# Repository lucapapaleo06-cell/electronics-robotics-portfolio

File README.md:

# Electronics & Robotics Portfolio

Electronic Engineering student at **Politecnico di Torino**, currently at **Tongji University** through the **POLITONG** program.

I was part of the **embedded branch of [Team ISAAC](https://github.com/Team-Isaac-Polito)** (2025–2026), where I designed the team's [LoRa remote kill switch](pcb-lora-kill-switch/). The team took part in the **RoboCup 2026 Rescue Robot League** in Korea, finishing **21st** as the **only Italian team**.

This repository collects my personal electronics and robotics projects: PCB design, embedded firmware and computer vision.

## Projects

| Project | What it is | Technologies | Status |
|---|---|---|---|
| [RoboCup Junior Rescue Line robot](robocup-junior-rescue-line/) | Line-following robot with computer vision for green intersection markers, plus a custom line-sensor PCB and 3D-printed chassis (team project) | Arduino, Raspberry Pi, Python, OpenCV, TensorFlow Lite, KiCad | Competed for three seasons, reached the national finals in the last one |
| [Arduino Mega shield](pcb-arduino-mega-shield/) | Main board of the RoboCup Junior robot: plugs onto an Arduino Mega and wires up sensors, motor driver and servos | KiCad, Gerber | Manufactured and used in competition |
| [LoRa remote kill switch](pcb-lora-kill-switch/) | Transmitter and receiver boards for a wireless emergency stop (Team ISAAC) | Altium Designer, RP2040, LoRa | Manufactured and tested |
| [Vision-controlled robotic hand](vision-robotic-hand/) | A webcam tracks my hand and a 5-servo robotic hand copies the finger positions | Python, OpenCV, MediaPipe, Arduino | Prototype |

The RoboCup Junior robot and its Mega shield were built together with Niccolò, Eleonora, Francesco and Ercolini.

## Repository layout

```
pcb-arduino-mega-shield/      KiCad project, schematic and PCB PDFs, Gerber files
pcb-lora-kill-switch/         Schematic + PCB PDFs, layout images, interactive 3D PDFs
vision-robotic-hand/          Python hand tracking + Arduino servo firmware
robocup-junior-rescue-line/   Arduino firmware, Raspberry Pi vision, line-sensor PCB, STL files
media/                        Renders and images used in the READMEs
```

## Tools

KiCad · Altium Designer · Arduino · Raspberry Pi · RP2040 · Python · OpenCV · MediaPipe · TensorFlow Lite · 3D printing

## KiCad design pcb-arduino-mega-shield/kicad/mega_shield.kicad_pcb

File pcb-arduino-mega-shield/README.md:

# Arduino Mega Shield

Main interface board for my RoboCup Junior Rescue Line robot ([robocup-junior-rescue-line](../robocup-junior-rescue-line/)). It plugs onto an **Arduino Mega**. It replaces loose jumper wires with labelled connectors for every sensor and actuator on the robot.

Part of the RoboCup Junior project built together with **Niccolò, Eleonora, Francesco and Ercolini** (their names are on the silkscreen, next to the team logo).

## Connectors on the board

- 3 × I²C headers for **VL53L0X time-of-flight** distance sensors (SDA/SCL)
- **Gyroscope** header with interrupt pin
- 2 × **TCS3200 colour sensor** headers (S0–S3, OUT, LED)
- Line-sensor input header on analog pins A1–A7
- **TB6612FNG motor driver** header (PWM A/B) and motor outputs
- 2 × **servo** headers
- 12 V power input

## Files

| Path | Content |
|---|---|
| `kicad/` | KiCad project (`.kicad_pro`, `.kicad_sch`, `.kicad_pcb`) |
| `images/mega_shield_schematic.pdf` | Schematic, exported with `kicad-cli` |
| `images/mega_shield_pcb.pdf` | PCB prints, one page per layer (front copper, back copper, silkscreen, outline) |
| `images/mega_shield_layout.svg` | Copper and silkscreen layout |
| `fabrication/mega_shield_gerber.zip` | Gerber and drill files for manufacturing |

## Tools

KiCad (the shield outline uses the Arduino Due/Mega form factor symbol)

## Status

Manufactured and used in competition.

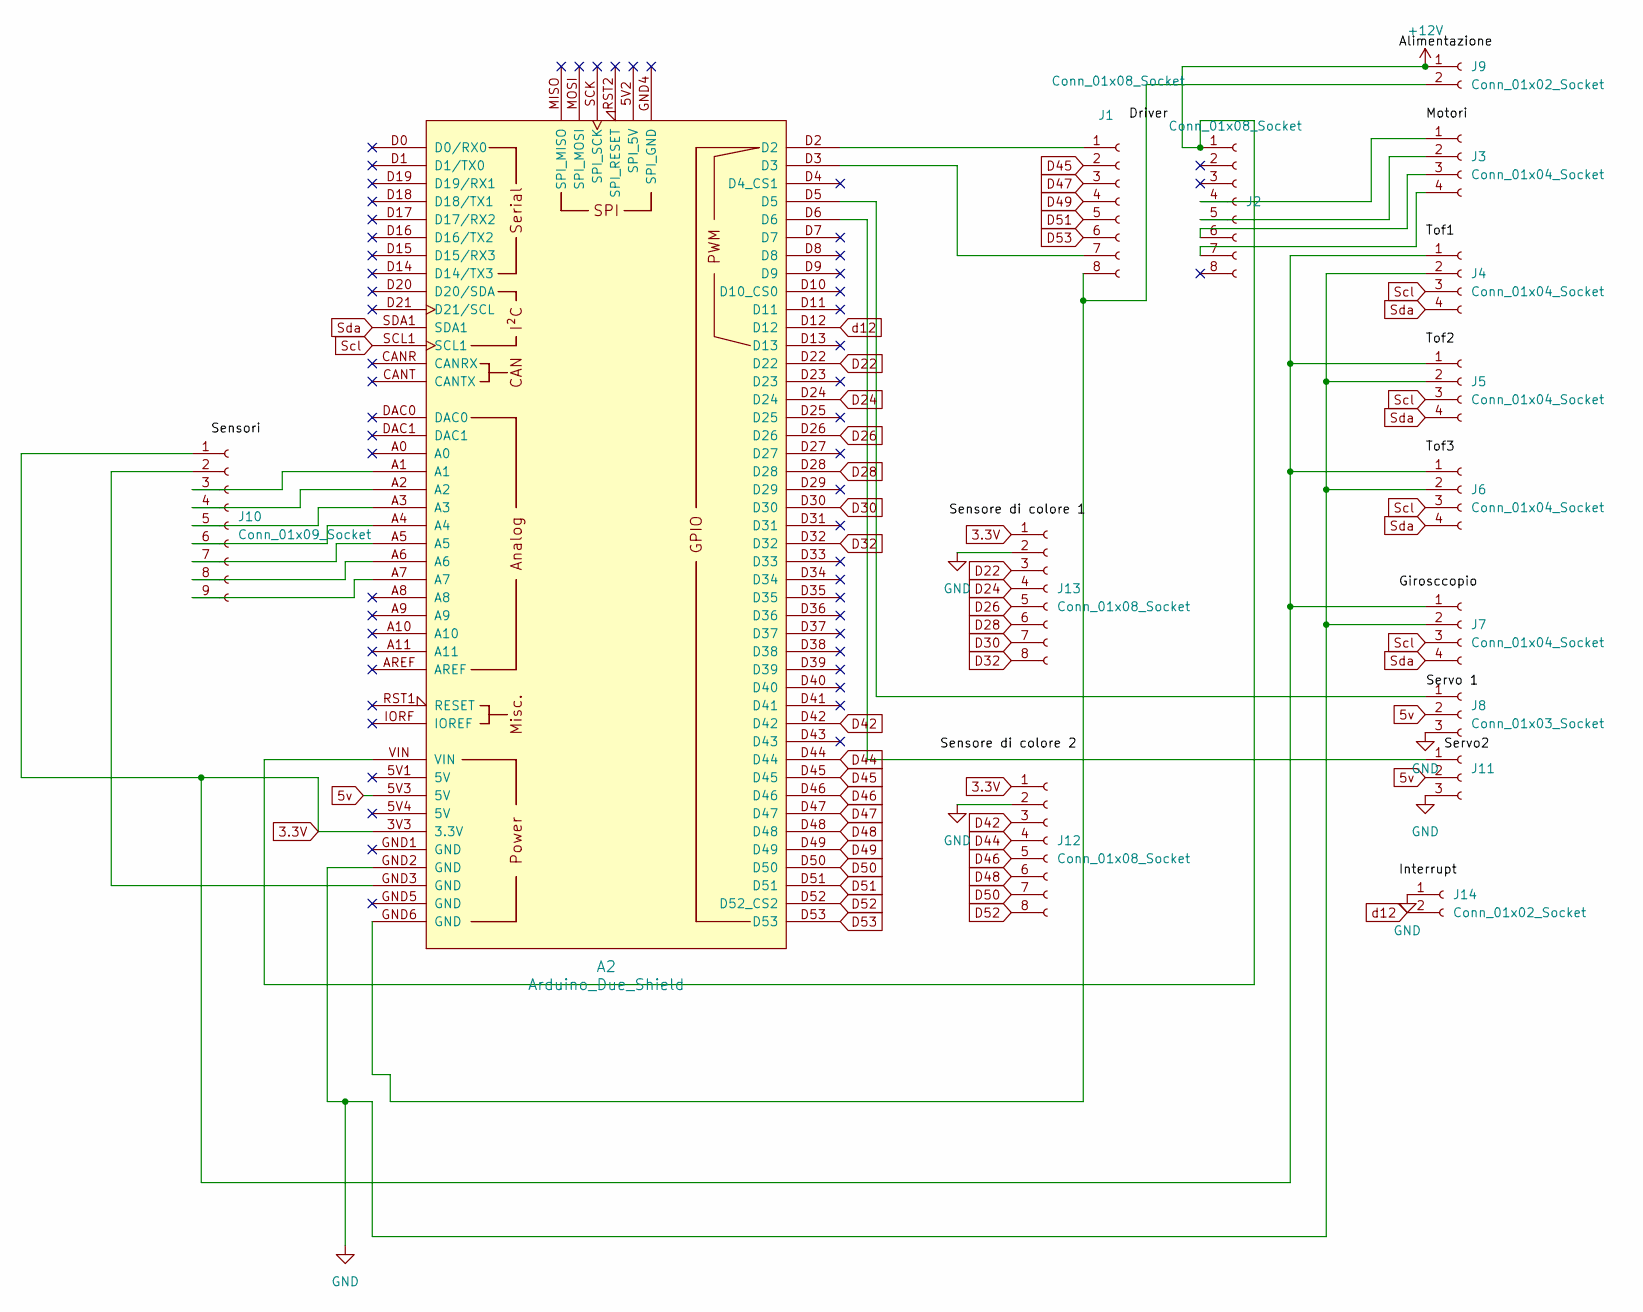
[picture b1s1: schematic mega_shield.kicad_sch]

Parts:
A2: Arduino_Due_Shield
J1, J2, J12, J13: Conn_01x08_Socket; PinSocket_1x08_P2.54mm_Vertical
J3, J4, J5, J6, J7: Conn_01x04_Socket; PinSocket_1x04_P2.54mm_Vertical
J8, J11: Conn_01x03_Socket; PinSocket_1x03_P2.54mm_Vertical
J9: Conn_01x02_Socket; AMASS_XT30UPB-F_1x02_P5.0mm_Vertical
J10: Conn_01x09_Socket; PinSocket_1x09_P2.54mm_Vertical
J14: Conn_01x02_Socket; PinSocket_1x02_P2.54mm_Vertical

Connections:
3.3V: A2.3V3 (3.3V), J4.1, J5.1, J6.1, J7.1, J10.1, J12.1, J13.1
5v: A2.5V3 (5V), J8.2, J11.2
+12V: A2.VIN, J2.1, J9.1
D22: A2.D22, J13.3
D24: A2.D24, J13.4
D26: A2.D26, J13.5
D28: A2.D28, J13.6
D30: A2.D30, J13.7
D32: A2.D32, J13.8
D42: A2.D42, J12.3
D44: A2.D44, J12.4
D45: A2.D45, J1.2
D46: A2.D46, J12.5
D47: A2.D47, J1.3
D48: A2.D48, J12.6
D49: A2.D49, J1.4
D50: A2.D50, J12.7
D51: A2.D51, J1.5
D52: A2.D52 (D52_CS2), J12.8
D53: A2.D53, J1.6
GND: A2.GND2 (GND), J4.2, J5.2, J6.2, J7.2, J8.3, J11.3, J12.2, J13.2, J14.1
unnamed: A2.D2, J1.1
unnamed: A2.D3, J1.7
unnamed: A2.GND6 (GND), J1.8, J9.2
unnamed: J2.4, J3.1
unnamed: J2.5, J3.2
unnamed: J2.6, J3.3
unnamed: J2.7, J3.4
unnamed: A2.D5, J8.1
unnamed: A2.GND3 (GND), J10.2
unnamed: A2.A1, J10.3
unnamed: A2.A2, J10.4
unnamed: A2.A3, J10.5
unnamed: A2.A4, J10.6
unnamed: A2.A5, J10.7
unnamed: A2.A6, J10.8
unnamed: A2.A7, J10.9
unnamed: A2.D6, J11.1
Scl: A2.SCL1, J4.3, J5.3, J6.3, J7.3
Sda: A2.SDA1, J4.4, J5.4, J6.4, J7.4
d12: A2.D12, J14.2

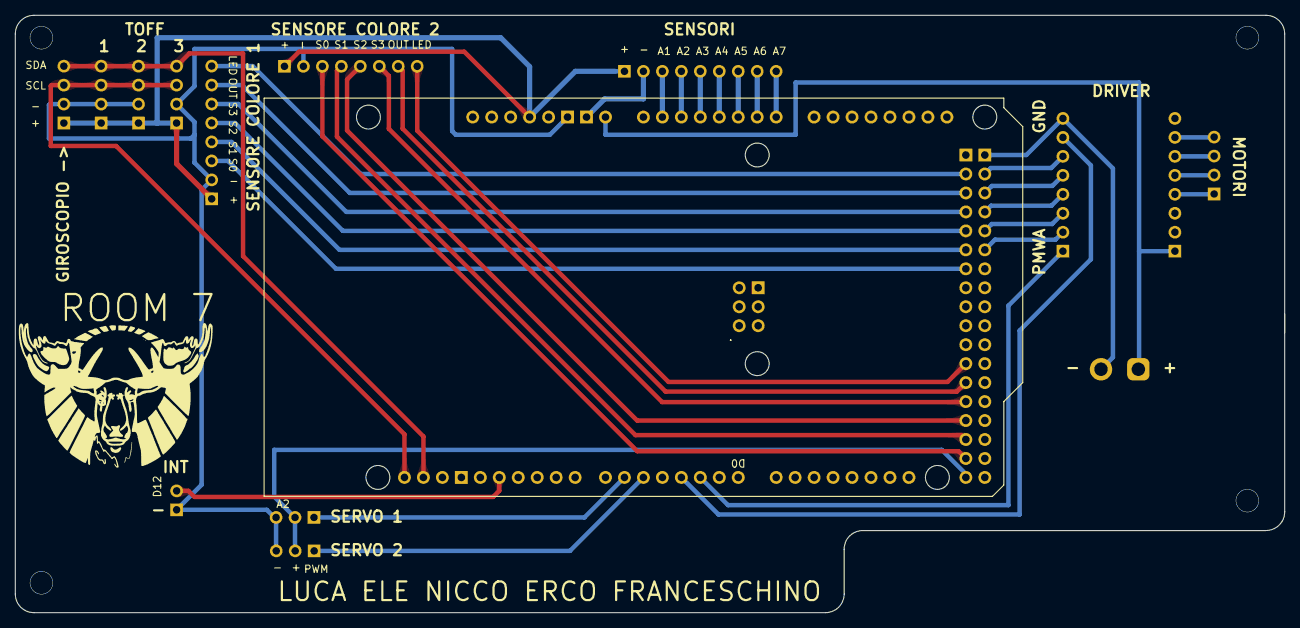
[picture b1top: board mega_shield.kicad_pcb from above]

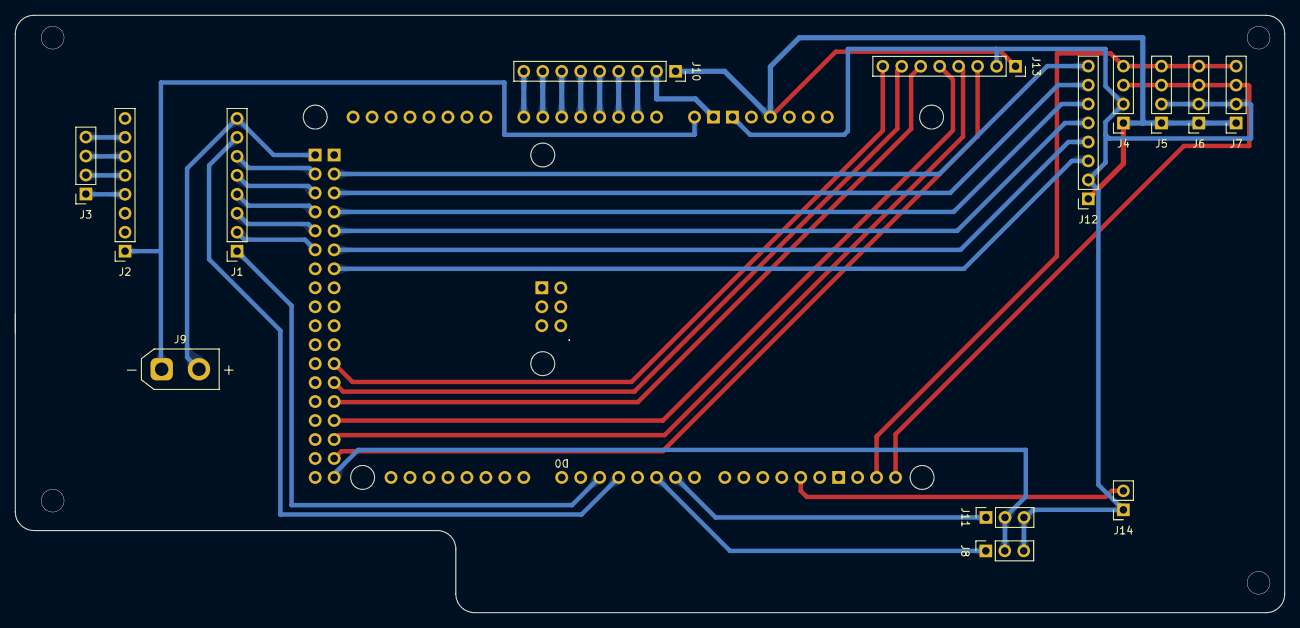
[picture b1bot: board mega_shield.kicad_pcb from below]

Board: 2 copper layers, 170.0 x 80.0 mm, 15 parts (15 on the bottom side), 41 nets.

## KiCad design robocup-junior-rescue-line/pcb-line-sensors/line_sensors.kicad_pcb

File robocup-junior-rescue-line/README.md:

# RoboCup Junior Rescue Line Robot – "Blecaut"

Autonomous robot for the **RoboCup Junior Rescue Line** challenge. Our team **competed for three seasons** and **reached the national finals** in the last one.

The robot follows a black line, handles green intersection markers and avoids obstacles. An **Arduino** runs the low-level control and a **Raspberry Pi** with a camera runs the computer vision. The two talk over serial.

## Team

Built together with **Niccolò, Eleonora, Francesco and Ercolini**. The robot, its boards and its code are a shared team effort.

## Contents

### `arduino/`: low-level control
| Sketch | Role |
|---|---|
| `seguiline_finale_sensori_di_colore_1.0` | Final line-following firmware (Arduino Mega): reflective line sensors, 2 × TCS3200 colour sensors for green markers, TB6612FNG motor driver, serial commands from the Raspberry Pi |
| `ultimo_nano_sensori_seguilinea_motori_12` | Line-following firmware for the Arduino Nano version of the robot |
| `2_seguilinea_completo_toff_seriale_1.0` | Line following with 2 × VL53L0X time-of-flight sensors for obstacle detection |
| `2_settaggio_sensori_di_colore_1.0` | Calibration tool for the colour sensors |

### `raspberry-pi/`: computer vision
| File | Role |
|---|---|
| `green_marker_detection.py` | Finds green markers and the black line using combined HSV + LAB masks. Uses contour geometry to decide the direction: **A**vanti (straight), **S**inistra (left), **D**estra (right), **I**nversione (U-turn). Sends it to the Arduino over serial |
| `color_calibration.py` | Trackbar tool to tune HSV/LAB thresholds on the field |
| `ball_detection.py` | Detects the balls in the evacuation zone with colour masks and Hough circles |
| `green_marker_classifier/` | TensorFlow Lite image classifier with the same four direction classes (A, I, D, S) |

### `pcb-line-sensors/`: custom line sensor board
8 × **CNY70** reflective sensors in an arc, with their resistors and a trimmer, on a single 8-pin output header. KiCad project, schematic and per-layer PCB PDFs (`images/`) and Gerber files (`fabrication/`). The main robot board is the [Arduino Mega shield](../pcb-arduino-mega-shield/).

### `3d/`: 3D-printed parts
Chassis body and cover (v2.2), wheel and motor gear, designed for 3D printing.

## Hardware

Arduino Mega / Arduino Nano · Raspberry Pi + camera · TB6612FNG motor driver · TCS3200 colour sensors · VL53L0X ToF sensors · CNY70 line sensors · gyroscope

## Software

Arduino (C++) · Python 3 · OpenCV · pyserial · TensorFlow Lite · KiCad

Serial ports in the Python scripts (`COM12`) are set for my development PC. Change them for the Raspberry Pi.

## Status

Competed for three seasons, reaching the national finals in the last one. The folders contain the final versions of the firmware and vision code.

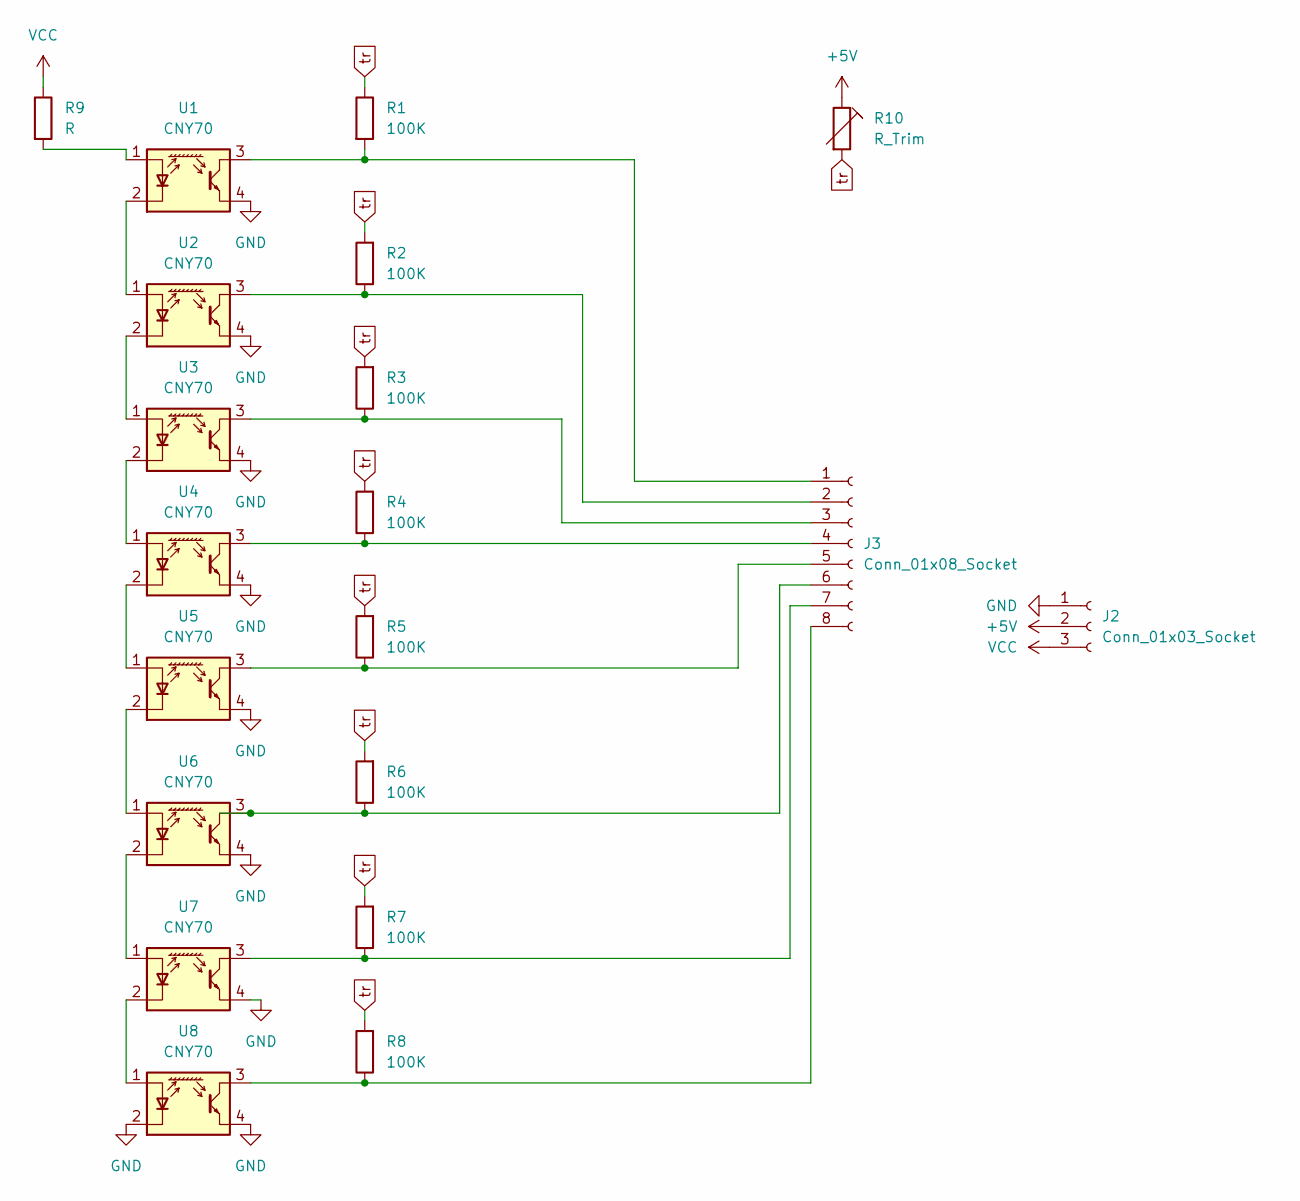
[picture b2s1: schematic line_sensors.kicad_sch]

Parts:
J2: Conn_01x03_Socket; PinSocket_1x03_P2.54mm_Vertical
J3: Conn_01x08_Socket; PinSocket_1x08_P2.54mm_Vertical
R1, R2, R3, R4, R5, R6, R7, R8: 100K; R_Axial_DIN0207_L6.3mm_D2.5mm_P7.62mm_Horizontal
R9: R; R_Axial_DIN0207_L6.3mm_D2.5mm_P7.62mm_Horizontal
R10: R_Trim; Potentiometer_Bourns_3296Y_Vertical
U1, U2, U3, U4, U5, U6, U7, U8: CNY70; Vishay_CNY70

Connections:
+5V: J2.2, R10.1
GND: J2.1, U1.4 (E), U2.4 (E), U3.4 (E), U4.4 (E), U5.4 (E), U6.4 (E), U7.4 (E), U8.2 (K), U8.4 (E)
unnamed: J3.1, R1.2, U1.3 (C)
unnamed: J3.2, R2.1, U2.3 (C)
unnamed: J3.3, R3.1, U3.3 (C)
unnamed: J3.4, R4.1, U4.3 (C)
unnamed: J3.5, R5.1, U5.3 (C)
unnamed: J3.6, R6.1, U6.3 (C)
unnamed: J3.7, R7.1, U7.3 (C)
unnamed: J3.8, R8.1, U8.3 (C)
unnamed: R9.2, U1.1 (A)
unnamed: U1.2 (K), U2.1 (A)
unnamed: U2.2 (K), U3.1 (A)
unnamed: U3.2 (K), U4.1 (A)
unnamed: U4.2 (K), U5.1 (A)
unnamed: U5.2 (K), U6.1 (A)
unnamed: U6.2 (K), U7.1 (A)
unnamed: U7.2 (K), U8.1 (A)
VCC: J2.3, R9.1
tr: R1.1, R2.2, R3.2, R4.2, R5.2, R6.2, R7.2, R8.2, R10.2

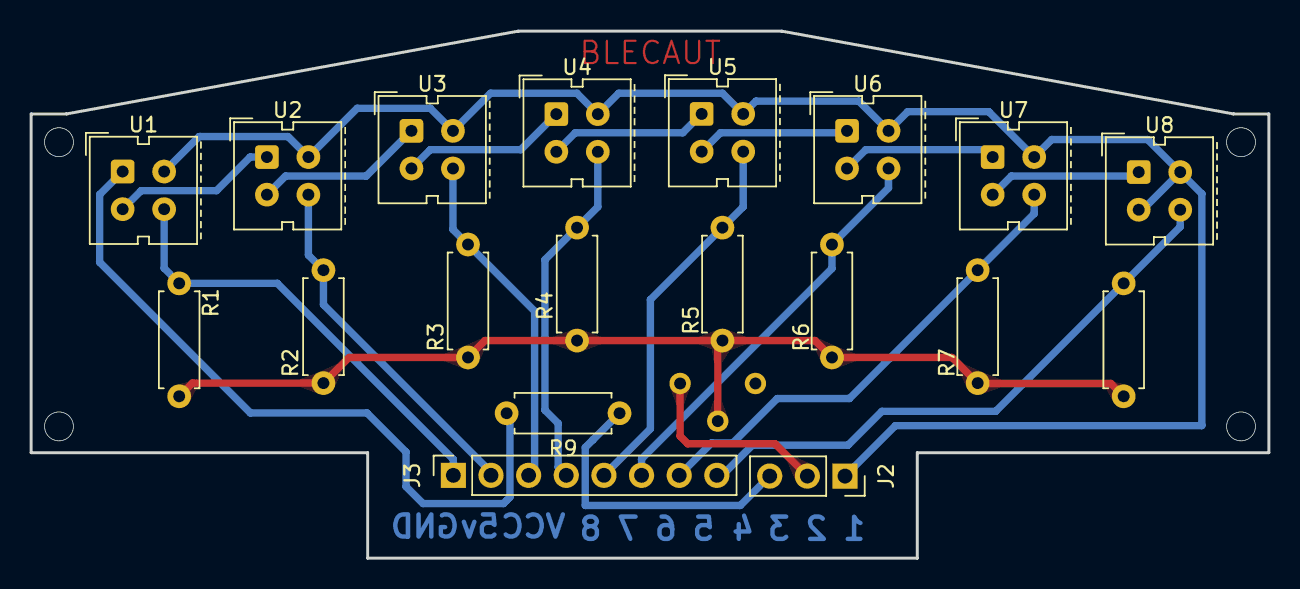
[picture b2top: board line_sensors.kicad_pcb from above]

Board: 2 copper layers, 83.5 x 35.6 mm, 20 parts (1 on the bottom side), 20 nets.
